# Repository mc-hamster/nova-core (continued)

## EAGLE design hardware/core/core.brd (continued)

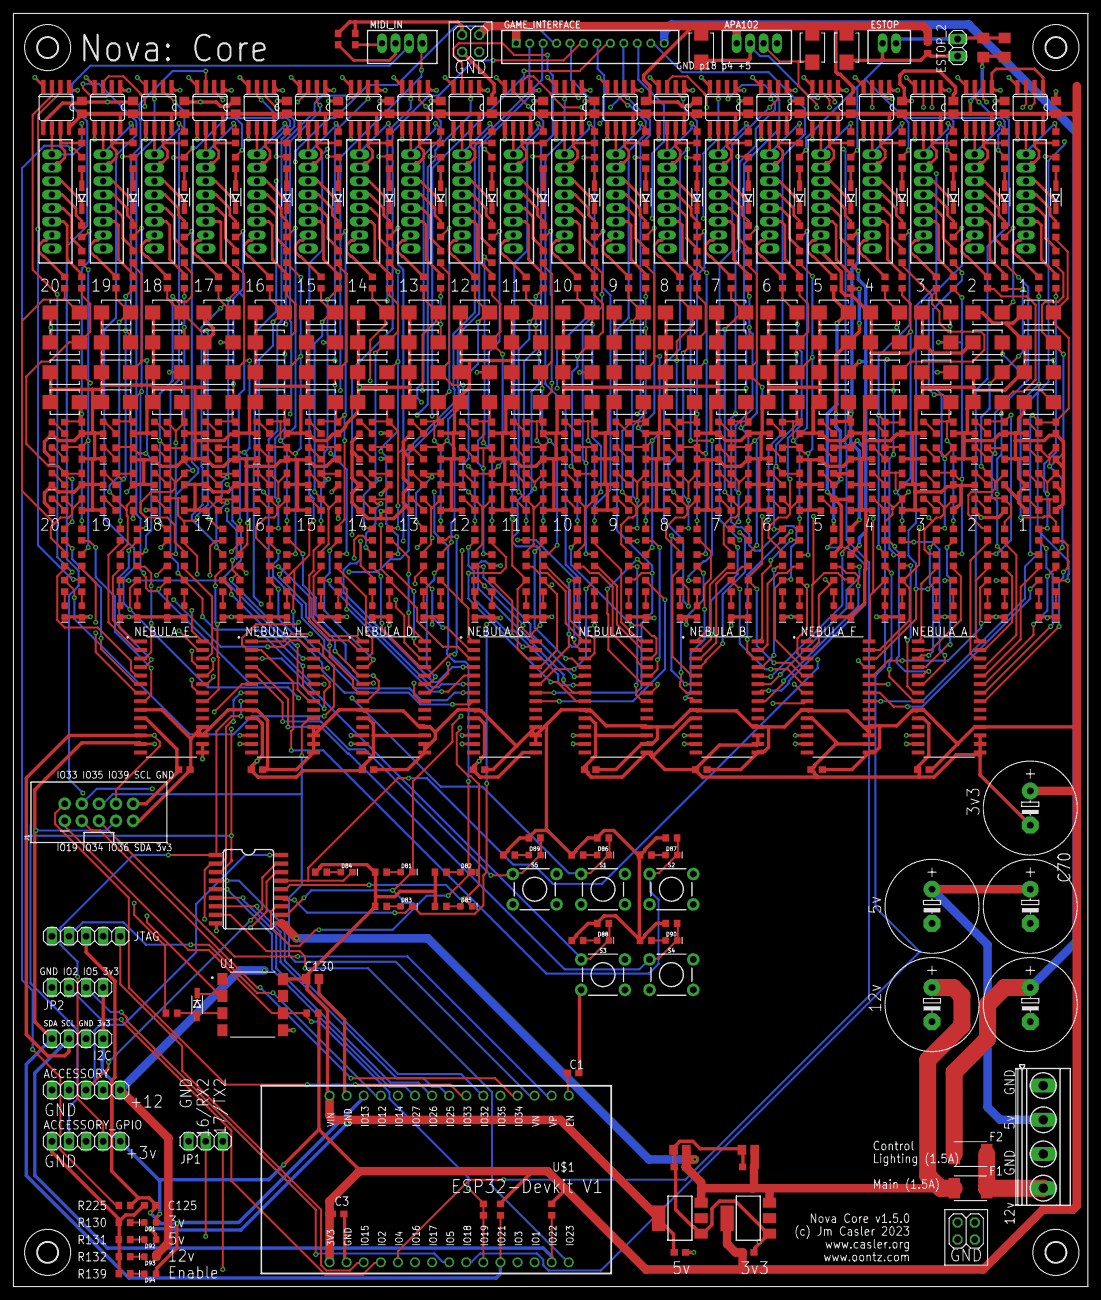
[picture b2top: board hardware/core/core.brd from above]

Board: 4 copper layers, 159.7 x 189.2 mm, 790 parts (0 on the bottom side), 547 nets.

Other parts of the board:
D199, D200, D201, D202, D203, D204, D205, D206, D207, D208, D209, D210, D211, D212, D213, D214, D215, D216, D217, D218, D219, D220, D221, D222, D223, D224, D225, D226, D227, D228, D229, D230, D231, D232, D233, D234, D235, D236, D237, D238: LED-0603
JP1: 1X03
R308, R309, R311, R312, R313, R314, R315, R316, R317, R318, R319, R320, R321, R322, R323, R324, R325, R326, R327, R328, R329, R330, R331, R332, R333, R334, R335, R336, R337, R338, R339, R340, R341, R342, R343, R344, R345, R346, R347, R348: 1k; R0603

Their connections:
16/RX2: JP1.2; also elsewhere on the board
17/TX2: JP1.3; also elsewhere on the board
F0: R309.1; also elsewhere on the board
F1: R308.1; also elsewhere on the board
F2: R312.1; also elsewhere on the board
F3: R311.1; also elsewhere on the board
F4: R314.1; also elsewhere on the board
F5: R313.1; also elsewhere on the board
F6: R316.1; also elsewhere on the board
F7: R315.1; also elsewhere on the board
F8: R318.1; also elsewhere on the board
F9: R317.1; also elsewhere on the board
F10: R320.1; also elsewhere on the board
F11: R319.1; also elsewhere on the board
F12: R322.1; also elsewhere on the board
F13: R321.1; also elsewhere on the board
F14: R324.1; also elsewhere on the board
F15: R323.1; also elsewhere on the board
G0: R326.1; also elsewhere on the board
G1: R325.1; also elsewhere on the board
G2: R328.1; also elsewhere on the board
G3: R327.1; also elsewhere on the board
G4: R330.1; also elsewhere on the board
G5: R329.1; also elsewhere on the board
G6: R332.1; also elsewhere on the board
G7: R331.1; also elsewhere on the board
G8: R334.1; also elsewhere on the board
G9: R333.1; also elsewhere on the board
G10: R336.1; also elsewhere on the board
G11: R335.1; also elsewhere on the board
G12: R338.1; also elsewhere on the board
G13: R337.1; also elsewhere on the board
G14: R340.1; also elsewhere on the board
G15: R339.1; also elsewhere on the board
GND: D199.C, D200.C, D201.C, D202.C, D203.C, D204.C, D205.C, D206.C, D207.C, D208.C, D209.C, D210.C, D211.C, D212.C, D213.C, D214.C, D215.C, D216.C, D217.C, D218.C, D219.C, D220.C, D221.C, D222.C, D223.C, D224.C, D225.C, D226.C, D227.C, D228.C, D229.C, D230.C, D231.C, D232.C, D233.C, D234.C, D235.C, D236.C, D237.C, D238.C, JP1.1; also elsewhere on the board
H0: R342.1; also elsewhere on the board
H1: R341.1; also elsewhere on the board
H2: R344.1; also elsewhere on the board
H3: R343.1; also elsewhere on the board
H4: R346.1; also elsewhere on the board
H5: R345.1; also elsewhere on the board
H6: R348.1; also elsewhere on the board
H7: R347.1; also elsewhere on the board
unnamed: D199.A, R308.2
unnamed: D200.A, R309.2
unnamed: D201.A, R311.2
unnamed: D202.A, R312.2
unnamed: D203.A, R313.2
unnamed: D204.A, R314.2
unnamed: D205.A, R315.2
unnamed: D206.A, R316.2
unnamed: D207.A, R317.2
unnamed: D208.A, R318.2
unnamed: D209.A, R319.2
unnamed: D210.A, R320.2
unnamed: D211.A, R321.2
unnamed: D212.A, R322.2
unnamed: D213.A, R323.2
unnamed: D214.A, R324.2
unnamed: D215.A, R325.2
unnamed: D216.A, R326.2
unnamed: D217.A, R327.2
unnamed: D218.A, R328.2
unnamed: D219.A, R329.2
unnamed: D220.A, R330.2
unnamed: D221.A, R331.2
unnamed: D222.A, R332.2
unnamed: D223.A, R333.2
unnamed: D224.A, R334.2
unnamed: D225.A, R335.2
unnamed: D226.A, R336.2
unnamed: D227.A, R337.2
unnamed: D228.A, R338.2
unnamed: D229.A, R339.2
unnamed: D230.A, R340.2
unnamed: D231.A, R341.2
unnamed: D232.A, R342.2
unnamed: D233.A, R343.2
unnamed: D234.A, R344.2
unnamed: D235.A, R345.2
unnamed: D236.A, R346.2
unnamed: D237.A, R347.2
unnamed: D238.A, R348.2

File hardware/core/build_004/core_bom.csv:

Comment,Designator,Footprint,LCSC Part #
,ESTOP_2,1X02,
,I2C,1X04,
,JP2,1X04,
,ACCESSORY,1X05,
,ACCESSORY_GPIO,1X05,
,JTAG,1X05,
,JP3,2X02,
,JP4,2X02,
,J1,2X5-SHROUDED,
,D1,LED-0603,C2286
,D2,LED-0603,C2286
,D3,LED-0603,C72043
,D4,LED-0603,C72041
,D5,LED-0603,C2290
,D6,LED-0603,C2286
,D7,LED-0603,C72043
,D8,LED-0603,C72041
,D9,LED-0603,C2290
,D10,LED-0603,C2286
,D11,LED-0603,C72043
,D12,LED-0603,C72041
,D13,LED-0603,C2290
,D14,LED-0603,C2286
,D15,LED-0603,C72043
,D16,LED-0603,C72041
,D17,LED-0603,C2290
,D18,LED-0603,C2286
,D19,LED-0603,C72043
,D20,LED-0603,C72041
,D21,LED-0603,C2290
,D22,LED-0603,C2286
,D23,LED-0603,C72043
,D24,LED-0603,C72041
,D25,LED-0603,C2290
,D26,LED-0603,C2286
,D27,LED-0603,C72043
,D28,LED-0603,C72041
,D29,LED-0603,C2290
,D30,LED-0603,C2286
,D31,LED-0603,C72043
,D32,LED-0603,C72041
,D33,LED-0603,C2290
,D34,LED-0603,C2286
,D35,LED-0603,C72043
,D36,LED-0603,C72041
,D37,LED-0603,C2290
,D38,LED-0603,C2286
,D39,LED-0603,C72043
,D40,LED-0603,C72041
,D41,LED-0603,C2290
,D42,LED-0603,C2286
,D43,LED-0603,C72043
,D44,LED-0603,C72041
,D45,LED-0603,C2290
,D46,LED-0603,C2286
,D47,LED-0603,C72043
,D48,LED-0603,C72041
,D49,LED-0603,C2290
,D50,LED-0603,C72043
,D51,LED-0603,C72041
,D52,LED-0603,C2290
,D53,LED-0603,C2286
,D54,LED-0603,C72043
,D55,LED-0603,C72041
,D56,LED-0603,C2290
,D57,LED-0603,C2286
,D58,LED-0603,C72043
,D59,LED-0603,C72041
,D60,LED-0603,C2290
,D61,LED-0603,C2286
,D62,LED-0603,C72043
,D63,LED-0603,C72041
,D64,LED-0603,C2290
,D65,LED-0603,C2286
,D66,LED-0603,C72043
,D67,LED-0603,C72041
,D68,LED-0603,C2290
,D69,LED-0603,C2286
,D70,LED-0603,C72043
,D71,LED-0603,C72041
,D72,LED-0603,C2290
,D73,LED-0603,C2286
,D74,LED-0603,C72043
,D75,LED-0603,C72041
,D76,LED-0603,C2290
,D77,LED-0603,C2286
,D78,LED-0603,C72043
,D79,LED-0603,C72041
,D80,LED-0603,C2290
,ULN2,SO18L,C9683
1k,R3 R4 R5 R6 R7 R8 R9 R10 R11 R12 R13 R14 R15 R16 R17 R18 R19 R20 R21 R22 R23 R24 R25 R28 R29 R30 R31 R32 R33 R34 R35 R36 R37 R38 R39 R40 R41 R42 R43 R44 R45 R46 R47 R48 R49 R50 R51 R52 R53 R66 R69 R70 R71 R72 R73 R74 R75 R76 R77 R78 R79 R80 R81 R82 R87 R88 R89 R90 R91 R92 R93 R94 R95 R96 R97 R98 R99 R100 R101 R102 R125 R126 R127 R128 R129 R130 R139,R0603,C21190
1nf,C124,C0603,C1588
1uf,C4 C6 C14 C15 C16 C17 C18 C19 C20 C21 C22 C23 C24 C25 C26 C27 C28 C29 C30 C31 C32 C33 C130,C0805,C15849
2.2k,R131,R0603,C4190
6N138SDM,U1,COUPL_6N138SDM,C188666
10,R68 R138,R1206,C17903
10k,R67 R133 R134 R135 R136 R137,R0603,C25804
10uf,C1 C2 C3 C5 C7 C8 C9 C10 C11 C12 C13 C34 C35 C36,C0603,C19702
68,R54 R55 R56 R57 R58 R59 R60 R61 R62 R63 R64 R65 R83 R84 R85 R86 R103 R104 R105 R106 R140 R141 R142 R143 R144 R145 R146 R147 R148 R149 R150 R151 R152 R153 R154 R155 R156 R157 R158 R159 R160 R161 R162 R163 R164 R165 R166 R167 R168 R169 R170 R171 R172 R173 R174 R175 R176 R177 R178 R179 R180 R181 R182 R183 R184 R185 R186 R187 R188 R189 R190 R191 R192 R193 R194 R195 R196 R197 R198 R199 R200 R201 R202 R203 R204 R205 R206 R207 R208 R209 R210 R211 R212 R213 R214 R215 R216 R217 R218 R219 R226 R227 R228 R229 R230 R231 R232 R233 R234 R235 R236 R237 R238 R239 R240 R241 R242 R243 R244 R245 R246 R247 R248 R249 R250 R251 R252 R253 R254 R255 R256 R257 R258 R259 R260 R261 R262 R263 R264 R265 R266 R267 R268 R269 R270 R271 R272 R273 R274 R275 R276 R277 R278 R279 R280 R281 R282 R283 R284 R285 R286 R287 R288 R289 R290 R291 R292 R293 R294 R295 R296 R297 R298 R299 R300 R301 R302 R303 R304 R305,R0603,c27592
100nf,C37 C38 C39 C40 C41 C42 C43 C44 C45 C46 C47 C48 C49 C50 C51 C52 C53 C54 C55 C56 C57 C58 C59 C60 C61 C62 C63 C64 C65 C66 C67 C68 C73 C74 C75 C76 C77 C78 C79 C80 C81 C82 C83 C84 C85 C86 C87 C88 C93 C94 C95 C96 C97 C98 C99 C100 C101 C102 C103 C104 C105 C106 C107 C108 C109 C110 C111 C112 C113 C114 C115 C116 C117 C118 C119 C120 C121 C122 C123,C0603,C14663
120,R1 R2 R107 R108 R109 R110 R111 R112 R113 R114 R115 R116 R117 R118 R119 R120 R121 R122 R123 R124,R0603,C22787
2200uf,C69 C70 C71 C72 C89 C90,E5-13,
B2B-PH-K,ESTOP,B2B-PH-K,
B4B-PH-K,APA102 MIDI_IN,B4B-PH-K,
B8B-PH-K,STAR_1 STAR_2 STAR_3 STAR_4 STAR_5 STAR_6 STAR_7 STAR_8 STAR_9 STAR_10 STAR_11 STAR_12 STAR_13 STAR_14 STAR_15 STAR_16 STAR_17 STAR_18 STAR_19 STAR_20,B8B-PH-K,C157974
B12B-PH-K,GAME_INTERFACE,B12B-PH-K,C158028
C_1NF/50V_0603,C125,C0603,C1588
C_100NF/50V_0603,C126 C127,C0603,C14663
D_B5819W-SL_CHANGJ_SOD123,D95 D96 D97 D98 D99 D100 D101 D102 D103 D104 D105 D106 D107 D108 D109 D110 D111 D112 D113 D114 D198,SOD123,C8598
ESP32DEVKITV1,U$1,ESP32-DEVKITV1,
LD117AS12TR,IC2 IC22,SOT223,C347222
MAX481CSA,IC1 IC3 IC4 IC5 IC6 IC7 IC8 IC9 IC10 IC11 IC12 IC13 IC14 IC15 IC16 IC17 IC18 IC19 IC20 IC21,SO08,C8963
MCP23017-E/SO,NEBULA_A NEBULA_B NEBULA_C NEBULA_D NEBULA_E NEBULA_F NEBULA_G NEBULA_H,SOIC127P1030X265-28N,C629440
MF-MSMF-STYLE2_1,F1 F2,FUSC4632X160,C78695
MKDSN1 5/4-5 08,POWER_IN,MKDSN1 5/4-5 08,
MOMENTARY-SWITCH-SPST-PTH-6.0MM,S1 S2 S3 S4 S5,TACTILE_SWITCH_PTH_6.0MM,
R_1K_0603,R132 R225 R310,R0603,C21190
R_2K_0603,R26 R27,R0603,C22975
R_56R_0603,R221 R222,R0603,C25196
R_82R_0603,R224,R0603,C23255
R_220R_0603,R306 R307,R0603,C22962
R_270R_0603,R220 R223,R0603,C22966
SMBJ8.0CA,D115 D116 D117 D118 D119 D120 D121 D122 D123 D124 D125 D126 D127 D128 D129 D130 D131 D132 D133 D134 D135 D136 D137 D138 D139 D140 D141 D142 D143 D144 D145 D146 D147 D148 D149 D150 D151 D152 D153 D154 D155 D156 D157 D158 D159 D160 D161 D162 D163 D164 D165 D166 D167 D168 D169 D170 D171 D172 D173 D174 D175 D176 D177 D178 D179 D180 D181 D182 D183 D184 D185 D186 D187 D188 D189 D190 D191 D192 D193 D194 D195 D196 D197,DIOM4336X265N,C78757
blue,D83 D88 D93,LED-0603,C72041
green,D82 D87 D92,LED-0603,C72043
red,D81 D86 D91,LED-0603,C2286
white,D84 D89,LED-0603,C2290
yellow,D85 D90 D94,LED-0603,C72038

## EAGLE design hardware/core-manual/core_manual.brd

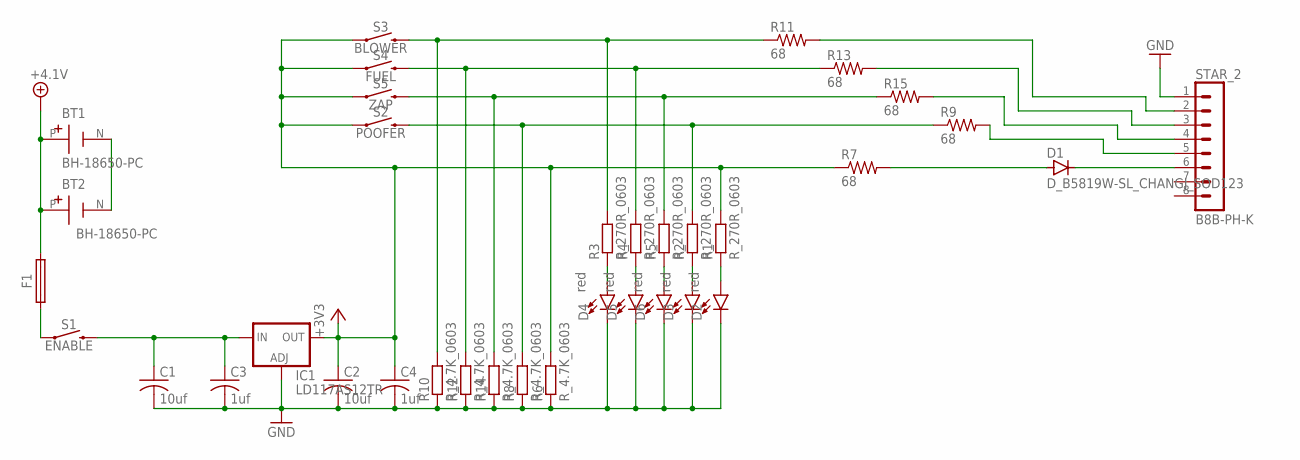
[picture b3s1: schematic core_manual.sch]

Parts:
BT1, BT2: BH-18650-PC; BAT_BH-18650-PC
C1, C2: 10uf; C0603; LCSC_PART C19702
C3, C4: 1uf; C0805; LCSC_PART C15849
D1: D_B5819W-SL_CHANGJ_SOD123; SOD123
D2, D3, D4, D5, D6: red; LED-0603; LCSC_PART C2286
F1: MF-MSMF-STYLE2_1; FUSC4632X160; LCSC_PART C78695
IC1: LD117AS12TR; SOT223; LCSC_PART C347222
R1, R2, R3, R4, R5: R_270R_0603; R0603
R6, R8, R10, R12, R14: R_4.7K_0603; R0603
R7, R9, R11, R13, R15: 68; R0603; LCSC_PART c27592
S1: ENABLE; TACTILE_SWITCH_PTH_6.0MM
S2: POOFER; TACTILE_SWITCH_PTH_6.0MM
S3: BLOWER; TACTILE_SWITCH_PTH_6.0MM
S4: FUEL; TACTILE_SWITCH_PTH_6.0MM
S5: ZAP; TACTILE_SWITCH_PTH_6.0MM
STAR_2: B8B-PH-K

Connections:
+3V3: C2.1, C4.1, IC1.4 (OUT), R1.2, R6.2, R7.1, S2.1, S3.1, S4.1, S5.1
+4.1V: BT1.P (+), BT2.P (+), F1.2
GND: C1.2, C2.2, C3.2, C4.2, D2.C, D3.C, D4.C, D5.C, D6.C, IC1.1 (ADJ), R6.1, R8.1, R10.1, R12.1, R14.1, STAR_2.1
unnamed: C1.1, C3.1, IC1.3 (IN), S1.3 (2)
unnamed: BT1.N (-), BT2.N (-)
unnamed: F1.1, S1.1
unnamed: R3.2, R10.2, R11.1, S3.3 (2)
unnamed: R4.2, R12.2, R13.1, S4.3 (2)
unnamed: R5.2, R14.2, R15.1, S5.3 (2)
unnamed: R2.2, R8.2, R9.1, S2.3 (2)
unnamed: R9.2, STAR_2.5
unnamed: R15.2, STAR_2.4
unnamed: R13.2, STAR_2.3
unnamed: R11.2, STAR_2.2
unnamed: D2.A, R1.1
unnamed: D3.A, R2.1
unnamed: D6.A, R5.1
unnamed: D5.A, R4.1
unnamed: D4.A, R3.1
unnamed: D1.A, R7.2
unnamed: D1.C, STAR_2.6

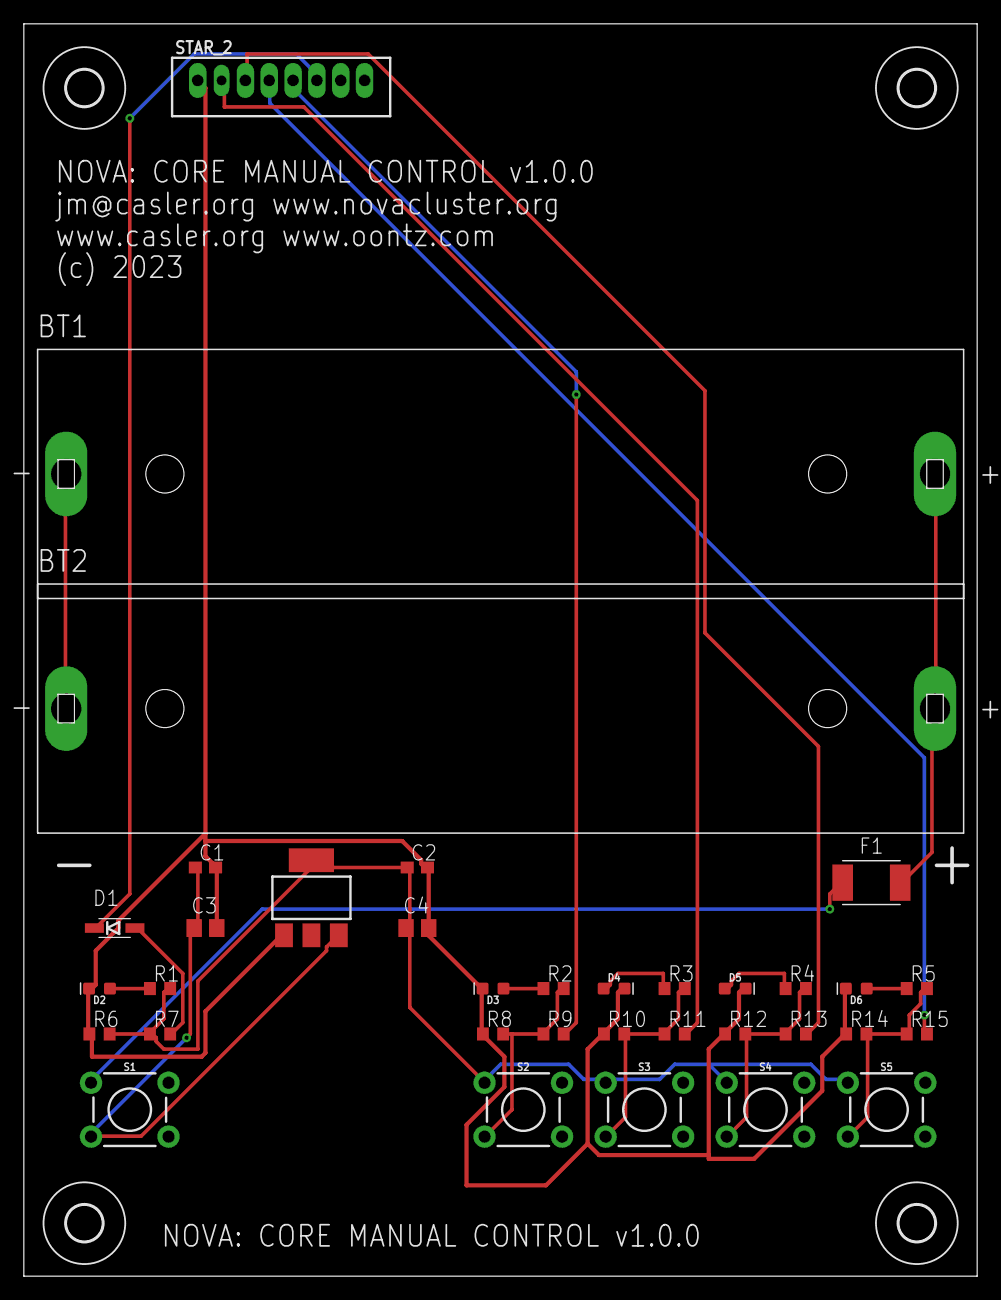
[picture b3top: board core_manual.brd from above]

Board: 2 copper layers, 80.0 x 105.1 mm, 39 parts (0 on the bottom side), 21 nets.

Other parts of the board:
H1, H2, H3, H4: MOUNT-HOLE3.0; 3,0

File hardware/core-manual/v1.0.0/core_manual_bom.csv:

Comment,Designator,Footprint,LCSC Part #
1uf,C3 C4,C0805,C15849
10uf,C1 C2,C0603,C19702
68,R7 R9 R11 R13 R15,R0603,c27592
B8B-PH-K,STAR_2,B8B-PH-K,
BH-18650-PC,BT1 BT2,BAT_BH-18650-PC,
BLOWER,S3,TACTILE_SWITCH_PTH_6.0MM,
D_B5819W-SL_CHANGJ_SOD123,D1,SOD123,C8598
ENABLE,S1,TACTILE_SWITCH_PTH_6.0MM,
FUEL,S4,TACTILE_SWITCH_PTH_6.0MM,
LD117AS12TR,IC1,SOT223,C347222
MF-MSMF-STYLE2_1,F1,FUSC4632X160,C78695
POOFER,S2,TACTILE_SWITCH_PTH_6.0MM,
R_4.7K_0603,R6 R8 R10 R12 R14,R0603,C23162
R_270R_0603,R1 R2 R3 R4 R5,R0603,C22966
ZAP,S5,TACTILE_SWITCH_PTH_6.0MM,
red,D2 D3 D4 D5 D6,LED-0603,C2286
